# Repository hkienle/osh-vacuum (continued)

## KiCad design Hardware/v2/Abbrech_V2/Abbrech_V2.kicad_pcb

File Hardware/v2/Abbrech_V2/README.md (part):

# Abbrechplatine V2 – LED-Streifen und Taster

Stand 2026-11-11 (Rev B, Mouse Bites). Ein Nutzen 70 × 81,2 mm mit einem Satz Zubehör-Platinen. Die Teilplatinen und die
Taster sind nicht untereinander verdrahtet: jede/jeder hat eigene Netze, auch die beiden Taster der Doppeltaster-Platine.

| Reihe | Teilplatinen (je 15,3 mm breit) |
|---|---|
| 0 | LED A 56 mm: 10 × WS2812B-2020 (V6, C52917434) |
| 1 | LED B 56 mm: 5 × WS2812B-5050 (V6, C52917433), Raster 7,8 mm wie V1, Pads quer |
| 2 | Einzeltaster T1 (17,3 mm) · Doppeltaster T5/T6 (32,5 mm, zwei Stecker) |
| 3 | Einzeltaster T2 · T3 · T4 |

Ringsum 5 mm Rand mit drei Passermarken, zwischen den Platinen 2 mm Fräsnut, Stege 5 mm mit Mouse Bites.

## Entscheidungen (Thomas)
- 2026-11-10: Breite 15,3 mm wie V1; Taster mit Bohrung an einem Ende und Halbbohrung am anderen; Taster TS-1187A-C-A-B
  (Extended, 2,6 N statt 1,6 N beim Basic-Teil, Hub bei Taktschaltern immer ≈ 0,25 mm); Stecker nicht bestückt, JLC bestückt
  nur die Oberseite; Bestellung bei JLC.
- 2026-11-10: LEDs exakt mittig.
- 2026-11-11: 5050-Streifen mit 5 LEDs, Pads quer zum Streifen.
- 2026-11-11 (später): keine THT-Löcher; alle Schraublöcher nur als Halbbohrung an den Enden (LED und Taster);
  Taster auf der Doppeltaster-Platine weiter auseinander (wie zwei Einzeltaster am Stück).
- 2026-11-11 (später): Stege auch zwischen den Taster-Reihen; je Kante ein Steg am Einzeltaster, zwei am Doppeltaster;
  alle Taster um 90° gedreht (Pads längs).
- 2026-11-11 (später): LED-Streifen zusätzlich mit THT-PH, um 90° gedreht neben den LEDs (u 7 / 49); SMD-PH nach innen; Doppeltaster ebenfalls mit THT-PH.
- 2026-11-11 (später): Einzeltaster zusätzlich mit THT-PH (B2B-PH-K, stehend, bestückt, Unterseite, bündig mit
  der Kante) dort, wo vorher die Beschriftung stand; der SMD-PH bleibt als Footprint, DNP; alle Taster-Platinen gleich
  ausgerichtet. (Kurz danach geändert: alle Stecker der Unterseite DNP, auch die THT-PH, siehe unten.)
- 2026-11-12 (später): Doppeltaster-Platine 32,5 mm statt 36,67 mm lang, an beiden Enden je 2,08 mm kürzer; Taster,
  Stecker, Leiterbahnen und Stege bleiben exakt an ihrem Platz.
- 2026-11-12 (später): Stege 5 mm statt 3 mm breit (JLC verlangt mind. 5 mm), je Seite 6 statt 4 Mouse-Bite-Bohrungen;
  Lage der Stege unverändert.
- 2026-11-12: Doppeltaster näher zusammen: Tastermitten 15,00 mm (vorher 19,33 mm); Stege an der Steckerseite und
  Siebdruck unten (Figma, Beschriftung der Doppeltaster mitgerückt) angepasst.
- 2026-11-11 (Umbau Rev B): alle Ecken so groß wie sinnvoll gerundet; Platinen mit Mouse Bites verbinden (V1 brach viel zu
  schwer, V-Cut erlaubt keine runden Ecken); LED-Streifen genau 56 mm; SMD- und THT-Stecker getrennt (SMD unten unter den
  LEDs, THT neben dem Schraubloch zur Kante versetzt); Taster kürzer (Schraubenkopf Ø 6 mm); eine Reihe Einzeltaster und
  eine Doppeltaster-Platine mit zwei Steckern („zwei Einzeltaster am Stück“); ein Satz je Nutzen; 4 Einzeltaster; Taster
  untereinander nicht verdrahtet. Vorbild: Abbrechteil der V1 („so in der Art grob“).

## Umsetzung
- **Maße**: Breite 15,3 mm, LED-Streifen 56 mm (V1), Eckradius 5 mm. An jedem Ende mittig eine Halbbohrung Ø 3,0 mm.
  Einzeltaster 17,33 mm (drei Stück plus zwei Nuten = 56 mm), Eckradius 4,5 mm (sonst lägen die Haltelaschen des
  SMD-Steckers in der Ecke), Taster mittig mit Pads längs. Doppeltaster 32,5 mm lang (seit 2026-11-12; vorher 36,67 mm wie zwei Einzeltaster am Stück), mittig im alten Feld,
  Tastermitten 15,00 mm auseinander (je 8,75 mm vom Ende), GND-Fläche in der Mitte geteilt.
- **Schraubenkopf Ø 6 mm**: oben im Umkreis 3 mm um jede Halbbohrung keine Bauteile und keine Lötstellen.
- **Pinbelegung 1:1 wie Hauptplatine** (gerade PH-Kabel): LED 1 GND, 2 Daten, 3 5V (J60); Taster 1 Schalter, 2 GND
  (J50–J52). Beschriftung unten je Pin `G D +` bzw. `S G`, dazu `IN`/`OUT` oben und unten.
- **Taster T1–T6**: zusätzlich JST PH THT stehend (B2B-PH-K-S, C131337, nicht bestückt) auf der
  Unterseite, Gehäuse endet bündig mit der Kante (Lochreihe 2,85 mm von der Kante). Alle Taster-Platinen liegen gleich im
  Nutzen (Stecköffnung des SMD-PH oben).
- **LED-Streifen**: an beiden Enden zusätzlich JST PH THT stehend (B3B-PH-K-S, C131339, nicht bestückt, Unterseite), um 90°
  gedreht (Lochreihe quer bei u 7 / 49, neben den LEDs); die SMD-PH (DNP) sitzen weiter
  innen bei u 20 / 36.
- **Stecker**: je Anschluss ein JST PH SMD liegend (S3B/S2B-PH-SM4-TB, nicht bestückt) auf der Unterseite unter den LEDs
  bzw. unter dem Taster, Öffnung bündig zur Längskante (0,65 mm zurück). Keine THT-Löcher.
- **LED-Streifen**: LEDs mittig, Datenkette von IN (rechts) nach OUT (links), 100 nF je LED, 10 µF am Eingang,
  5V-Schiene oben 0,8 mm, Einspeisung von beiden Steckern, GND-Flächen oben und unten.
  5050: VDD/DO oben, GND/DI unten, Daten mit 45° durch die Lücken, 100 nF senkrecht in der Lücke auf der Eingangsseite
  jeder LED. 2020: 100 nF längs über der LED, Pad 1 genau über dem VDD-Pad. 10 µF senkrecht zwischen THT-Stecker (Ausgang)
  und der ersten LED, Pad 1 auf der Schiene (Thomas 2026-11-11: weg vom Rand, kompakter).
- **Nutzen**: Fräsnut 2 mm, Stege 5 mm (Footprint `Abbrech_V2:MouseBites_Steg5mm_Nut2mm`: je Seite 6 NPTH Ø 0,5 mm im
  Raster 0,8 mm, Mitte 0,25 mm in der Platine, so bricht der Steg an der Platinenkante). Stege nur an den Längskanten (die
  Stirnseiten haben Halbbohrungen). LED-Streifen: drei Stege je Längskante zwischen den Stecköffnungen. Taster: je Kante
  ein Steg mittig unter dem Taster (Doppeltaster zwei); an der Steckerseite sitzt er mittig vor dem Stecker zwischen den
  Haltelaschen – der Stecker ist unten, das Gegenstück wird unter der Platine eingeschoben, ein Steg-Rest stört nicht.
  Die Sperrfläche des SMD-PH ragt dabei über die Kante (Gehäuse endet 0,15 mm vor den Bohrungen); deshalb ist die
  DRC-Prüfung „NPTH in Sperrfläche“ auf „ignorieren“ gestellt. Innenecken der Stege R 0,5 mm.
- **Siebdruck der LEDs**: Umrisse aller LEDs auf F.Fab (die Abblock-Kondensatoren sitzen dicht daneben); deshalb ist die DRC-Prüfung „Footprint weicht von Bibliothek ab“ auf „ignorieren“ gestellt.
- **3D-Modelle** für WS2812B-2020, TS-1187A und die PH-SMD-Stecker aus der JLCEDA/EasyEDA Official Library
  (https://lceda.cn/, https://easyeda.com), KiCad 10 liefert sie nicht mit; Herkunft in `3d/QUELLE.md`. Renders in
  `Review/abbrech/`.

- **Siebdruck oben und unten aus Figma** (2026-11-11): Rahmen „Abbrechplatine oben – Siebdruck“ und „Abbrechplatine
  unten – Siebdruck (Ansicht von unten)“ auf der Seite „Platine“ (Figma-Datei der Hauptplatine). Render schwarz, 20 px/mm,
  deckt genau den Nutzen ab; Ebene „Siebdruck (weiß = Druck)“. Export als SVG ohne Render nach
  `tools/abbrech/assets/silk_oben.svg` / `silk_unten.svg`, `gen_pcb.py` setzt sie als Flächen (unten gespiegelt) und lässt
  die generierten Texte weg. Schrift Jost Black (Netto Pro ist über die Figma-Schnittstelle nicht ladbar; in Figma
  umstellbar, dann neu exportieren).
- **STEP-Modelle** der herausgebrochenen Teilplatinen (ohne DNP-Teile): `step/Abbrech_LED_2020.step`,
  `Abbrech_LED_5050.step`, `Abbrech_Taster_einzeln.step`, `Abbrech_Taster_doppelt.step`, erzeugt mit
  `tools/abbrech/export_step.py` (KiCad-Python, aus 05_Hardware).

## Erzeugen und Prüfen
Alles wird aus Skripten erzeugt (nicht in KiCad von Hand ändern, sonst überschreibt der nächste Lauf die Änderung):

```
zsh tools/abbrech/build.sh                                   # Schaltplan, Layout, Flächen füllen, ERC + DRC mit Schaltplan-Abgleich
zsh tools/abbrech/fertigung.sh Fertigung/Abbrech_aktuell     # JLC: Gerber-ZIP, BOM, CPL (zu jedem Commit neu)
```
(beides aus `05_Hardware`). Stand 2026-11-11: ERC 0, DRC 0, Abgleich 0.

## Bestellung bei JLC
- 2 Lagen, 1,6 mm, 1 oz, Farbe wie Hauptplatine; „Panel by Customer“ (Nutzen mit Fräsnuten und Mouse Bites, keine
  V-Cuts); Vias „Tented“.
- „Different Design“: 4 (LED 2020, LED 5050, Einzeltaster, Doppeltaster).
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
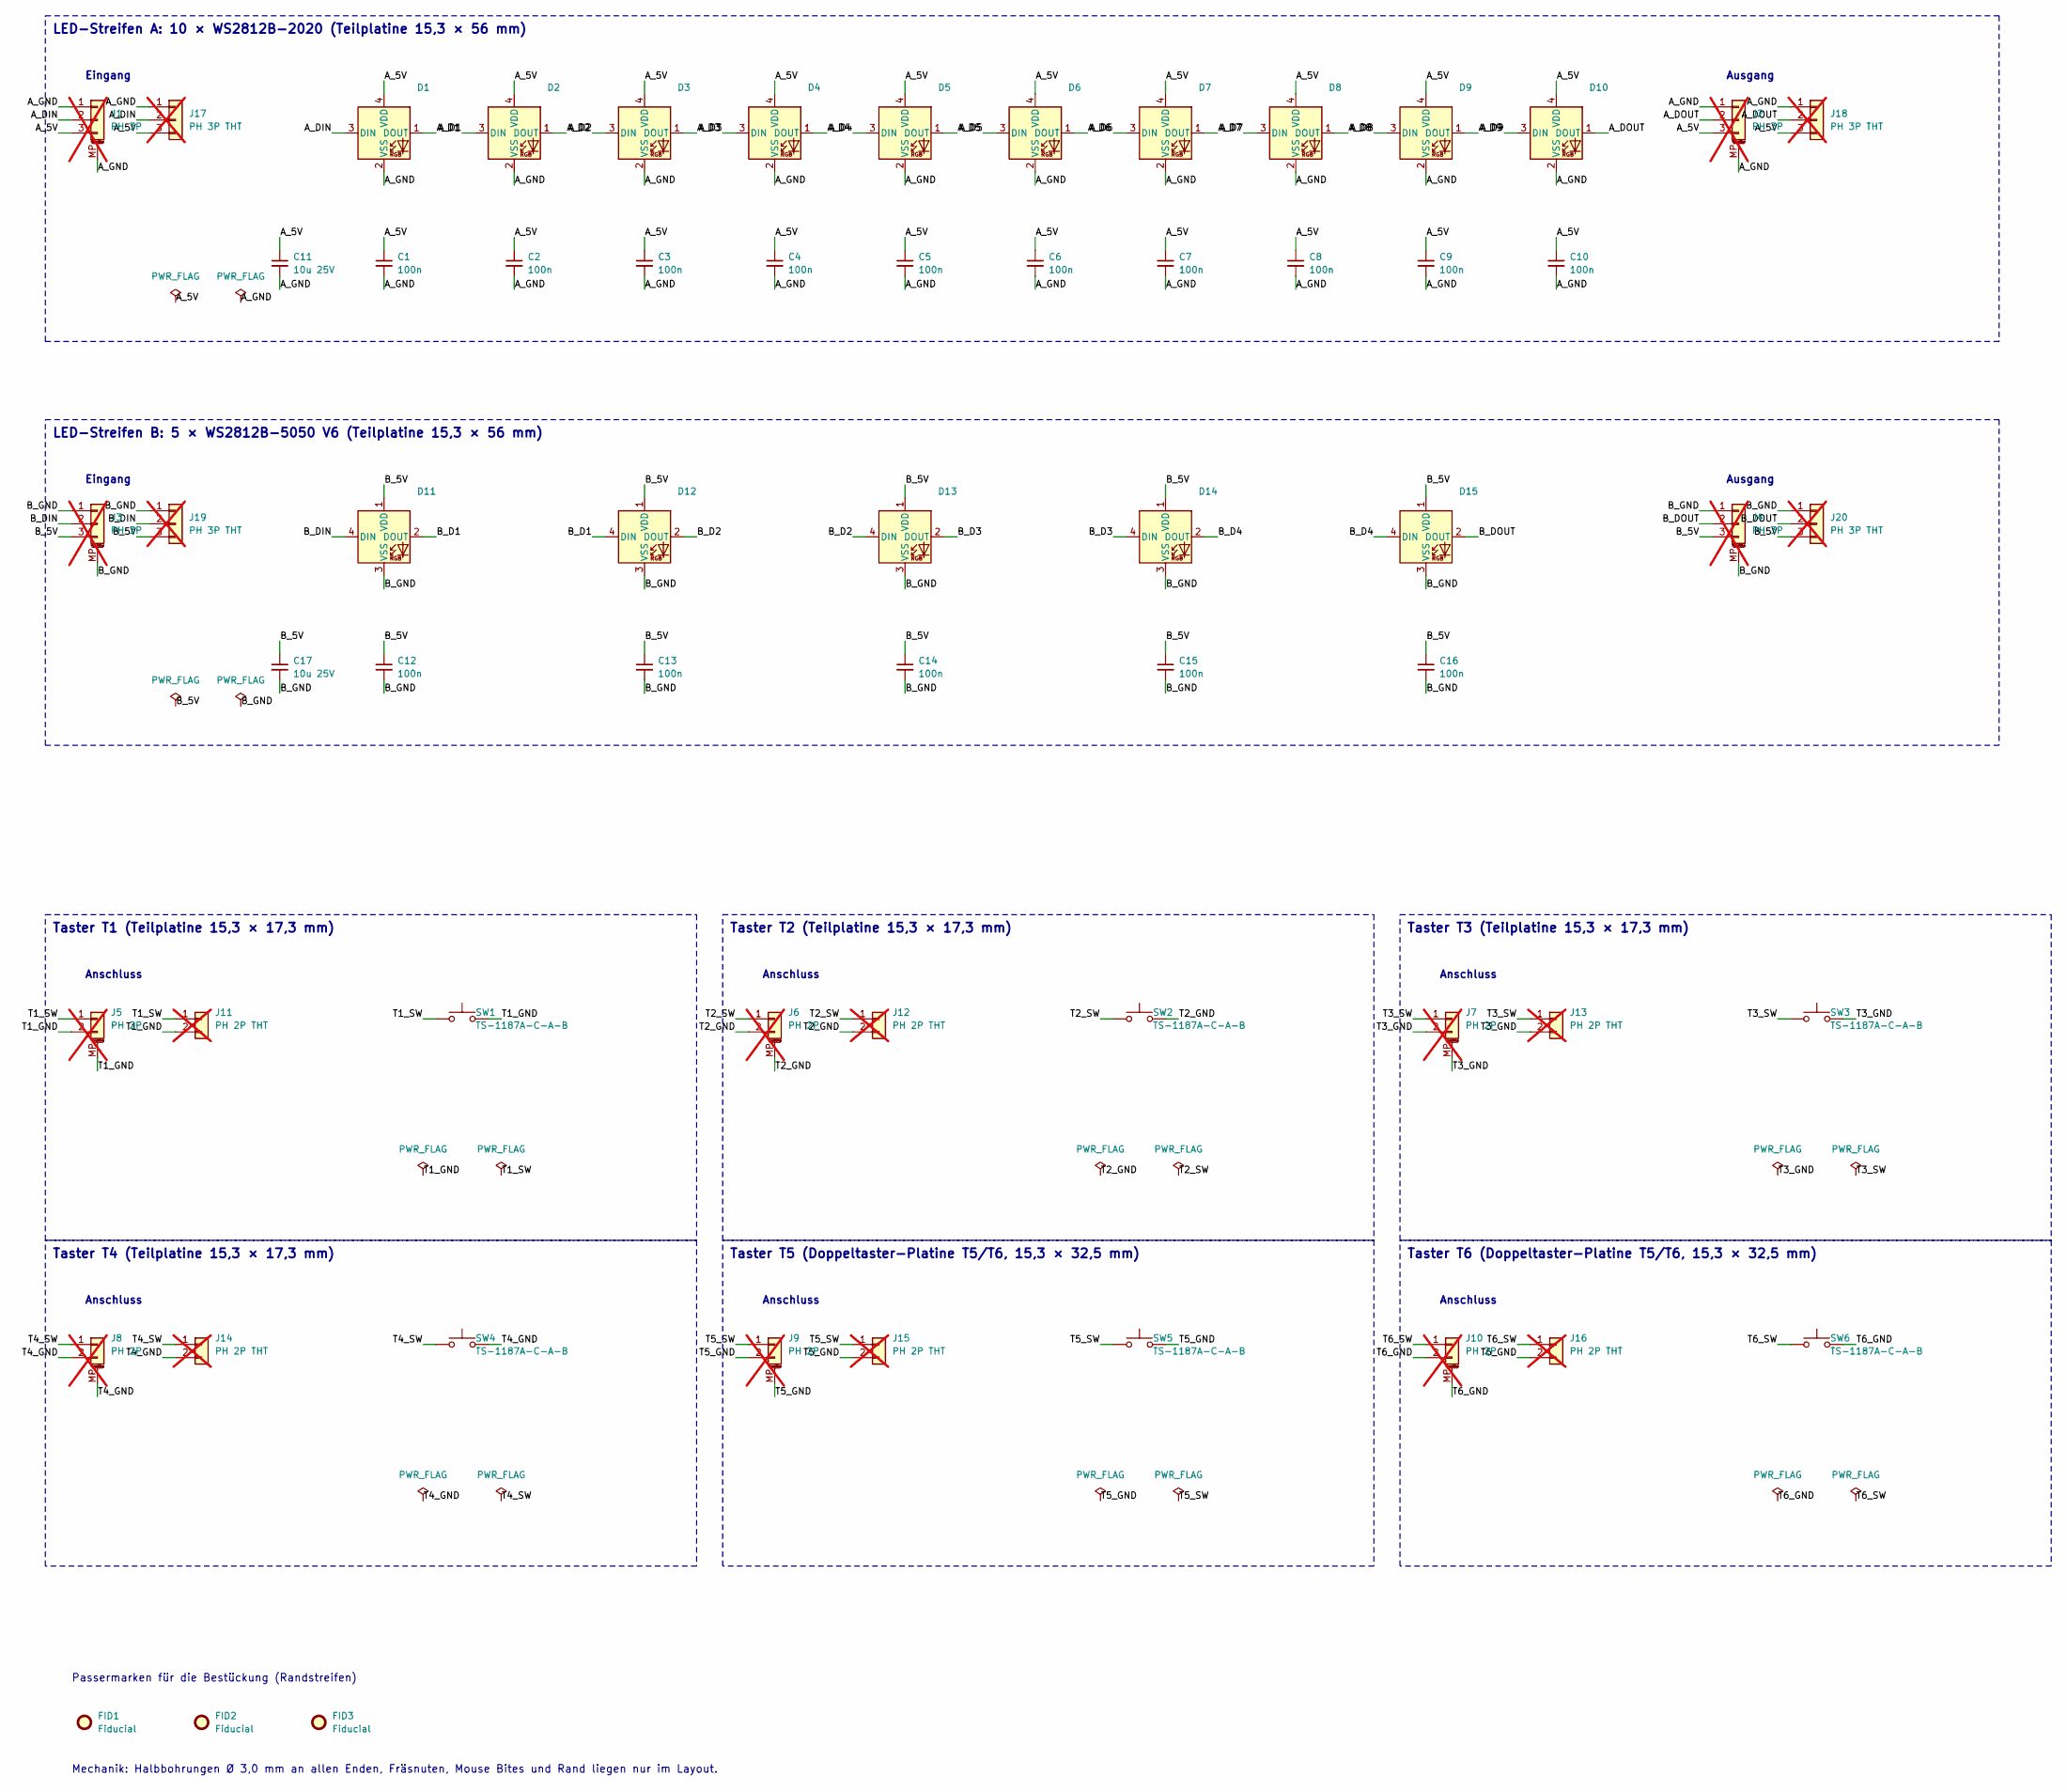
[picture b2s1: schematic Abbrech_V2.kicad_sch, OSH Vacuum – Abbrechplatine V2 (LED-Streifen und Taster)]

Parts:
C1, C2, C3, C4, C5, C6, C7, C8, C9, C10, C12, C13, C14, C15, C16: 100n; C_0402_1005Metric; MPN CL05B104KO5NNNC; LCSC C1525
C11, C17: 10u 25V; C_0603_1608Metric; MPN CL10A106MA8NRNC; LCSC C96446
D1, D2, D3, D4, D5, D6, D7, D8, D9, D10: WS2812B-2020; LED_WS2812B-2020_PLCC4_2.0x2.0mm; MPN WS2812B-2020-V6; LCSC C52917434
D11, D12, D13, D14, D15: WS2812B-5050; LED_WS2812B_PLCC4_5.0x5.0mm_P3.2mm; MPN WS2812B-V6; LCSC C52917433
FID1, FID2, FID3: Fiducial; Fiducial_1mm_Mask2mm
J1, J2, J3, J4: PH 3P; JST_PH_S3B-PH-SM4-TB_1x03-1MP_P2.00mm_Horizontal; MPN S3B-PH-SM4-TB(LF)(SN); LCSC C265101; not fitted
J5, J6, J7, J8, J9, J10: PH 2P; JST_PH_S2B-PH-SM4-TB_1x02-1MP_P2.00mm_Horizontal; MPN S2B-PH-SM4-TB(LF)(SN); LCSC C295747; not fitted
J11, J12, J13, J14, J15, J16: PH 2P THT; JST_PH_B2B-PH-K_1x02_P2.00mm_Vertical; MPN B2B-PH-K-S(LF)(SN); LCSC C131337; not fitted
J17, J18, J19, J20: PH 3P THT; JST_PH_B3B-PH-K_1x03_P2.00mm_Vertical; MPN B3B-PH-K-S(LF)(SN); LCSC C131339; not fitted
SW1, SW2, SW3, SW4, SW5, SW6: TS-1187A-C-A-B; SW_Push_1P1T_XKB_TS-1187A; MPN TS-1187A-C-A-B; LCSC C480267

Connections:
/A_5V: C1.1, C2.1, C3.1, C4.1, C5.1, C6.1, C7.1, C8.1, C9.1, C10.1, C11.1, D1.4 (VDD), D2.4 (VDD), D3.4 (VDD), D4.4 (VDD), D5.4 (VDD), D6.4 (VDD), D7.4 (VDD), D8.4 (VDD), D9.4 (VDD), D10.4 (VDD), J1.3, J2.3, J17.3, J18.3
/A_D1: D1.1 (DOUT), D2.3 (DIN)
/A_D2: D2.1 (DOUT), D3.3 (DIN)
/A_D3: D3.1 (DOUT), D4.3 (DIN)
/A_D4: D4.1 (DOUT), D5.3 (DIN)
/A_D5: D5.1 (DOUT), D6.3 (DIN)
/A_D6: D6.1 (DOUT), D7.3 (DIN)
/A_D7: D7.1 (DOUT), D8.3 (DIN)
/A_D8: D8.1 (DOUT), D9.3 (DIN)
/A_D9: D9.1 (DOUT), D10.3 (DIN)
/A_DIN: D1.3 (DIN), J1.2, J17.2
/A_DOUT: D10.1 (DOUT), J2.2, J18.2
/A_GND: C1.2, C2.2, C3.2, C4.2, C5.2, C6.2, C7.2, C8.2, C9.2, C10.2, C11.2, D1.2 (VSS), D2.2 (VSS), D3.2 (VSS), D4.2 (VSS), D5.2 (VSS), D6.2 (VSS), D7.2 (VSS), D8.2 (VSS), D9.2 (VSS), D10.2 (VSS), J1.1, J1.MP (MountPin), J2.1, J2.MP (MountPin), J17.1, J18.1
/B_5V: C12.1, C13.1, C14.1, C15.1, C16.1, C17.1, D11.1 (VDD), D12.1 (VDD), D13.1 (VDD), D14.1 (VDD), D15.1 (VDD), J3.3, J4.3, J19.3, J20.3
/B_D1: D11.2 (DOUT), D12.4 (DIN)
/B_D2: D12.2 (DOUT), D13.4 (DIN)
/B_D3: D13.2 (DOUT), D14.4 (DIN)
/B_D4: D14.2 (DOUT), D15.4 (DIN)
/B_DIN: D11.4 (DIN), J3.2, J19.2
/B_DOUT: D15.2 (DOUT), J4.2, J20.2
/B_GND: C12.2, C13.2, C14.2, C15.2, C16.2, C17.2, D11.3 (VSS), D12.3 (VSS), D13.3 (VSS), D14.3 (VSS), D15.3 (VSS), J3.1, J3.MP (MountPin), J4.1, J4.MP (MountPin), J19.1, J20.1
/T1_GND: J5.2, J5.MP (MountPin), J11.2, SW1.2
/T1_SW: J5.1, J11.1, SW1.1
/T2_GND: J6.2, J6.MP (MountPin), J12.2, SW2.2
/T2_SW: J6.1, J12.1, SW2.1
/T3_GND: J7.2, J7.MP (MountPin), J13.2, SW3.2
/T3_SW: J7.1, J13.1, SW3.1
/T4_GND: J8.2, J8.MP (MountPin), J14.2, SW4.2
/T4_SW: J8.1, J14.1, SW4.1
/T5_GND: J9.2, J9.MP (MountPin), J15.2, SW5.2
/T5_SW: J9.1, J15.1, SW5.1
/T6_GND: J10.2, J10.MP (MountPin), J16.2, SW6.2
/T6_SW: J10.1, J16.1, SW6.1

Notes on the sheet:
LED-Streifen A: 10 × WS2812B-2020 (Teilplatine 15,3 × 56 mm)
Eingang
Ausgang
LED-Streifen B: 5 × WS2812B-5050 V6 (Teilplatine 15,3 × 56 mm)
Taster T1 (Teilplatine 15,3 × 17,3 mm)
Anschluss
Taster T2 (Teilplatine 15,3 × 17,3 mm)
Taster T3 (Teilplatine 15,3 × 17,3 mm)
Taster T4 (Teilplatine 15,3 × 17,3 mm)
Taster T5 (Doppeltaster-Platine T5/T6, 15,3 × 32,5 mm)
Taster T6 (Doppeltaster-Platine T5/T6, 15,3 × 32,5 mm)
Passermarken für die Bestückung (Randstreifen)
Mechanik: Halbbohrungen Ø 3,0 mm an allen Enden, Fräsnuten, Mouse Bites und Rand liegen nur im Layout.

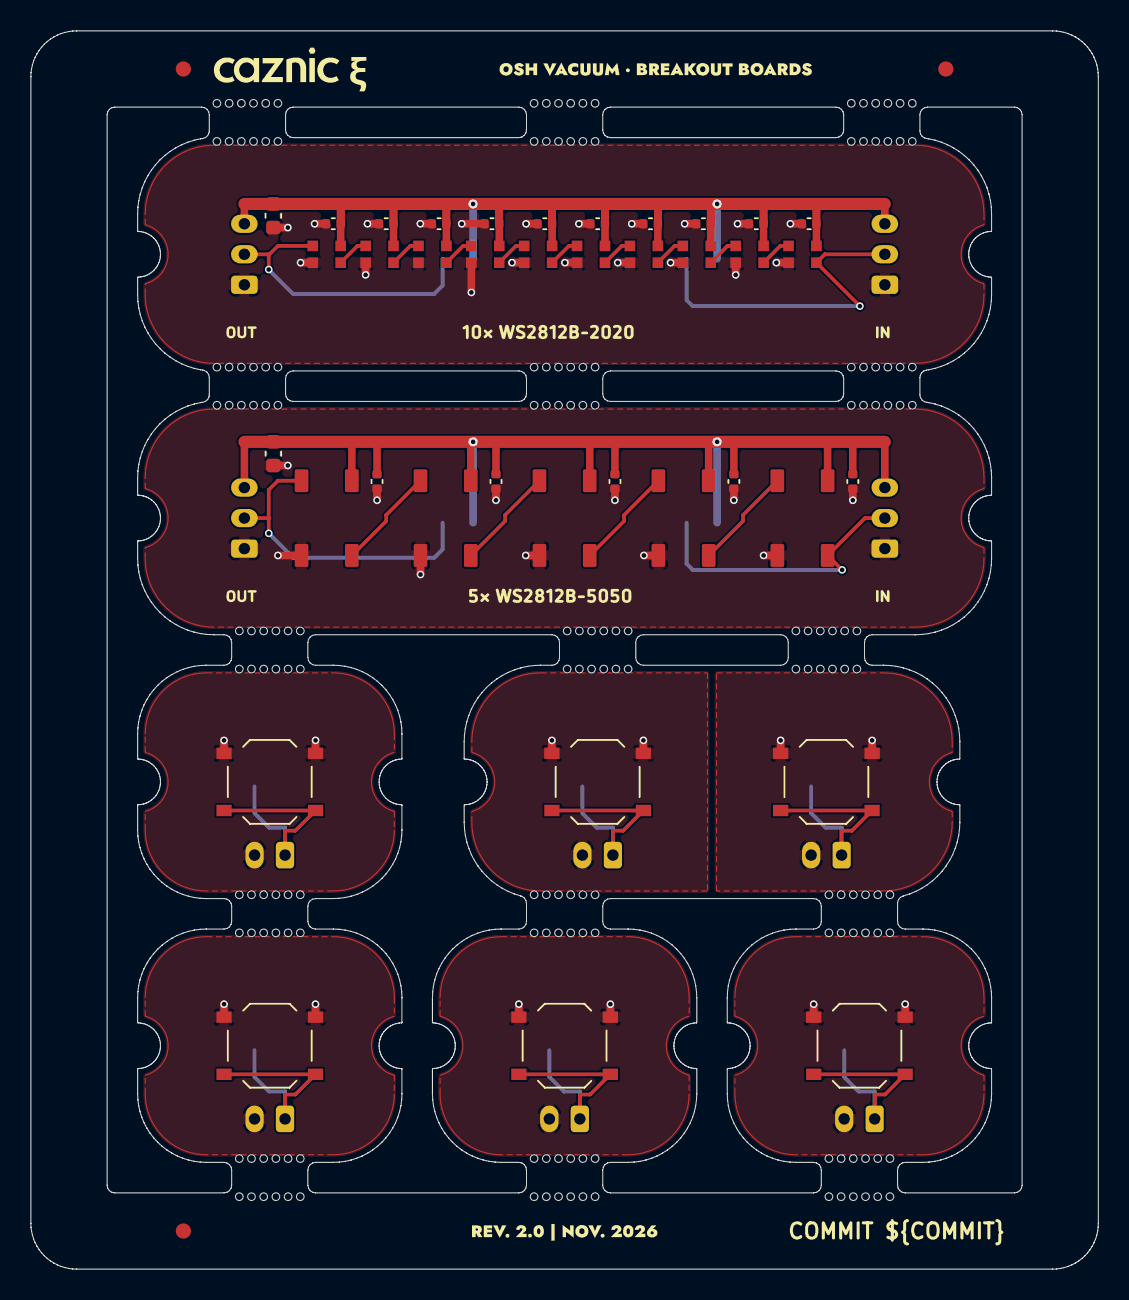
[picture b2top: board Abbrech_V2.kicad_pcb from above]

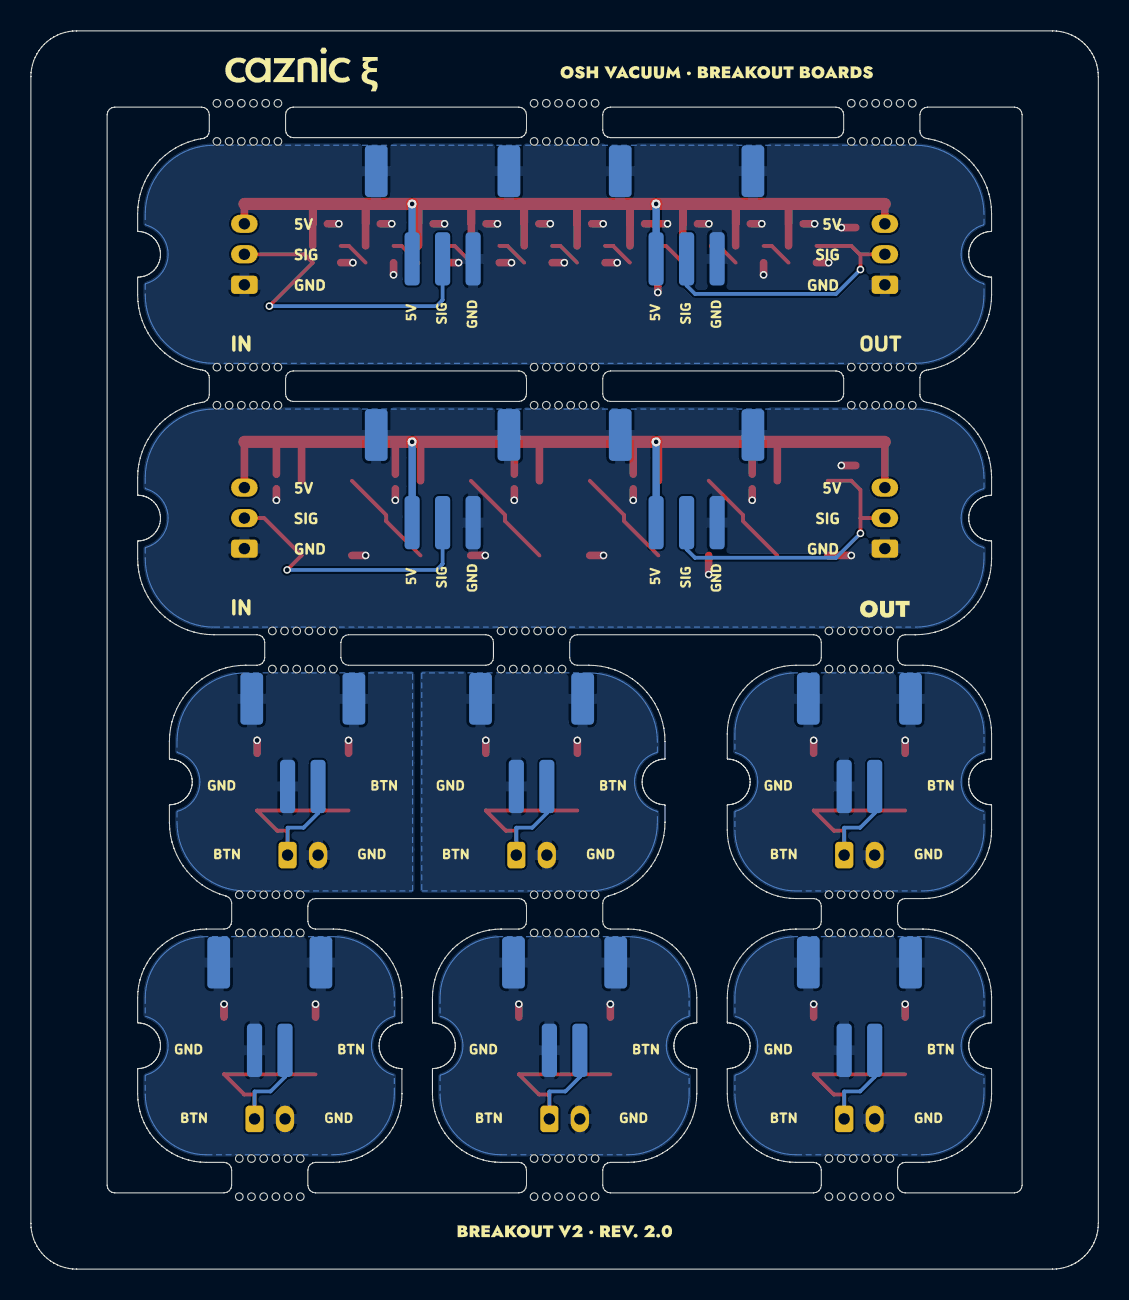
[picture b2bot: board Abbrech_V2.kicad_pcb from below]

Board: 2 copper layers, 70.0 x 81.2 mm, 76 parts (20 on the bottom side), 33 nets.

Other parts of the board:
MB1, MB2, MB3, MB4, MB5, MB6, MB7, MB8, MB9, MB10, MB11, MB12, MB13, MB14, MB15: MouseBites_Steg5mm_Nut2mm

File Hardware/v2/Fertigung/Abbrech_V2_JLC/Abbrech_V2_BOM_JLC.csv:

Comment,Designator,Footprint,LCSC Part #
100n,"C1,C10,C12,C13,C14,C15,C16,C2,C3,C4,C5,C6,C7,C8,C9",C_0402_1005Metric,C1525
TS-1187A-C-A-B,"SW1,SW2,SW3,SW4,SW5,SW6",SW_Push_1P1T_XKB_TS-1187A,C480267
WS2812B-5050,"D11,D12,D13,D14,D15",LED_WS2812B_PLCC4_5.0x5.0mm_P3.2mm,C52917433
WS2812B-2020,"D1,D10,D2,D3,D4,D5,D6,D7,D8,D9",LED_WS2812B-2020_PLCC4_2.0x2.0mm,C52917434
10u 25V,"C11,C17",C_0603_1608Metric,C96446

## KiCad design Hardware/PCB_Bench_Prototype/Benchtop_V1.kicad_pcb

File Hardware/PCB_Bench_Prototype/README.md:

# PCB Bench Prototype

**Status: Untested** - This board is currently in the benchtop prototype phase of the Open Source Vacuum Cleaner project and has not yet been tested.

## Overview

This PCB is designed to control a high RPM impeller for vacuum machines. It provides comprehensive control and monitoring capabilities with modern connectivity options.

The design features break-off sections that allow users to build their own vacuum cleaner in whichever shape they like. These break-off sections enable flexible placement of LEDs and buttons to suit various form factors and user preferences.

## Features

- **Connectivity**
  - BLE (Bluetooth Low Energy)
  - WiFi connectivity
  
- **Power Management**
  - USB-C connector for programming
  - Voltage regulation from 15-32V down to 5V and 3.3V
  - Battery voltage monitoring (reads voltage of connected battery)
  
- **User Interface**
  - 5 RGB LEDs (WS2812B)
  - 3 customizable buttons
  
- **Motor Control & Monitoring**
  - Automotive ProFet by Infineon for high-side switching (required for ESC control, replacing classic MOSFETs)
  - Level-shifted 3.3V and 5V PWM output
  - Voltage-divided input for 5V tachometer signal
  - 10kΩ thermistor reading capability
  
- **Expansion**
  - All unused and safe GPIOs are broken out
  - I2C, SPI, and UART interfaces available

## Bill of Materials (BOM)

| Designator | Footprint | Quantity | Value | LCSC Part # |
|------------|-----------|----------|-------|-------------|
| C1, C7, C8, C9 | 0805 | 4 | 22µF | - |
| C10, C11, C12, C13, C14, C2, C5 | 0805 | 7 | 0.1µF | - |
| C3 | 0805 | 1 | 1µF | - |
| C4 | 0805 | 1 | 10nF | - |
| C6 | 0805 | 1 | 10µF | - |
| LED1, LED2, LED3, LED4, LED5 | LED-SMD_4P-L5.0-W5.0-TL-1 | 5 | WS2812B-V5/W | C2874885 |
| R10 | 0805 | 1 | 330kΩ | - |
| R11 | 0805 | 1 | 33kΩ | - |
| R12 | 0805 | 1 | 56kΩ | - |
| R13 | 0805 | 1 | 4.7kΩ | - |
| R14, R16 | 0805 | 2 | 5.1kΩ | - |
| R15, R17, R18, R3, R5, R6, R7, R8 | 0805 | 8 | 10kΩ | - |
| R4 | 0805 | 1 | 220Ω | - |
| R9 | 0805 | 1 | 22kΩ | - |
| SW1, SW2 | SW-SMD_4P-L4.2-W3.2-P2.15-LS4.6 | 2 | RKB2SJK250SMTRLFS | C2927789 |
| SW6, SW7, SW8 | KEY-SMD_4P-L5.2-W5.2-P3.7-LS6.4-TL | 3 | TS-1076S-A7B3 | C492950 |
| U1 | WIRELM-SMD_ESP32-S3-WROOM-1 | 1 | ESP32-S3-WROOM-1(N16R2) | C2913205 |
| U2 | PG-HSOF-8_L10.4-W9.8-BTH500151LUAAUMA1 | 1 | BTH500151LUAAUMA1 | C36571656 |
| U3 | SOT-223-4_L6.5-W3.5-P2.30-LS7.0-BR | 1 | LD1117S33CTR | C35879 |
| U4, U5 | SC-70-5_L2.0-W1.3-P0.65-LS2.1-BL | 2 | SN74AHCT1G125DCKR | C350557 |
| U8 | PWRM-TH_L11.7-W7.5_TSR1-2450 | 1 | TSR 1-2450_C6886877 | C6886877 |
| U9 | USB-SMD_TYPE-C16PIN-1 | 1 | 12402012E212A | C5150972 |

## Images

### Front View

### Back View

### PCB Layout

## License

This hardware design is licensed under the **CERN Open Hardware Licence - Strongly Reciprocal (CERN OHL-S v2)**.

The full license text is available at: [cern_ohl_s_v2.txt](https://gitlab.com/ohwr/project/cernohl/-/wikis/uploads/819d71bea3458f71fba6cf4fb0f2de6b/cern_ohl_s_v2.txt)

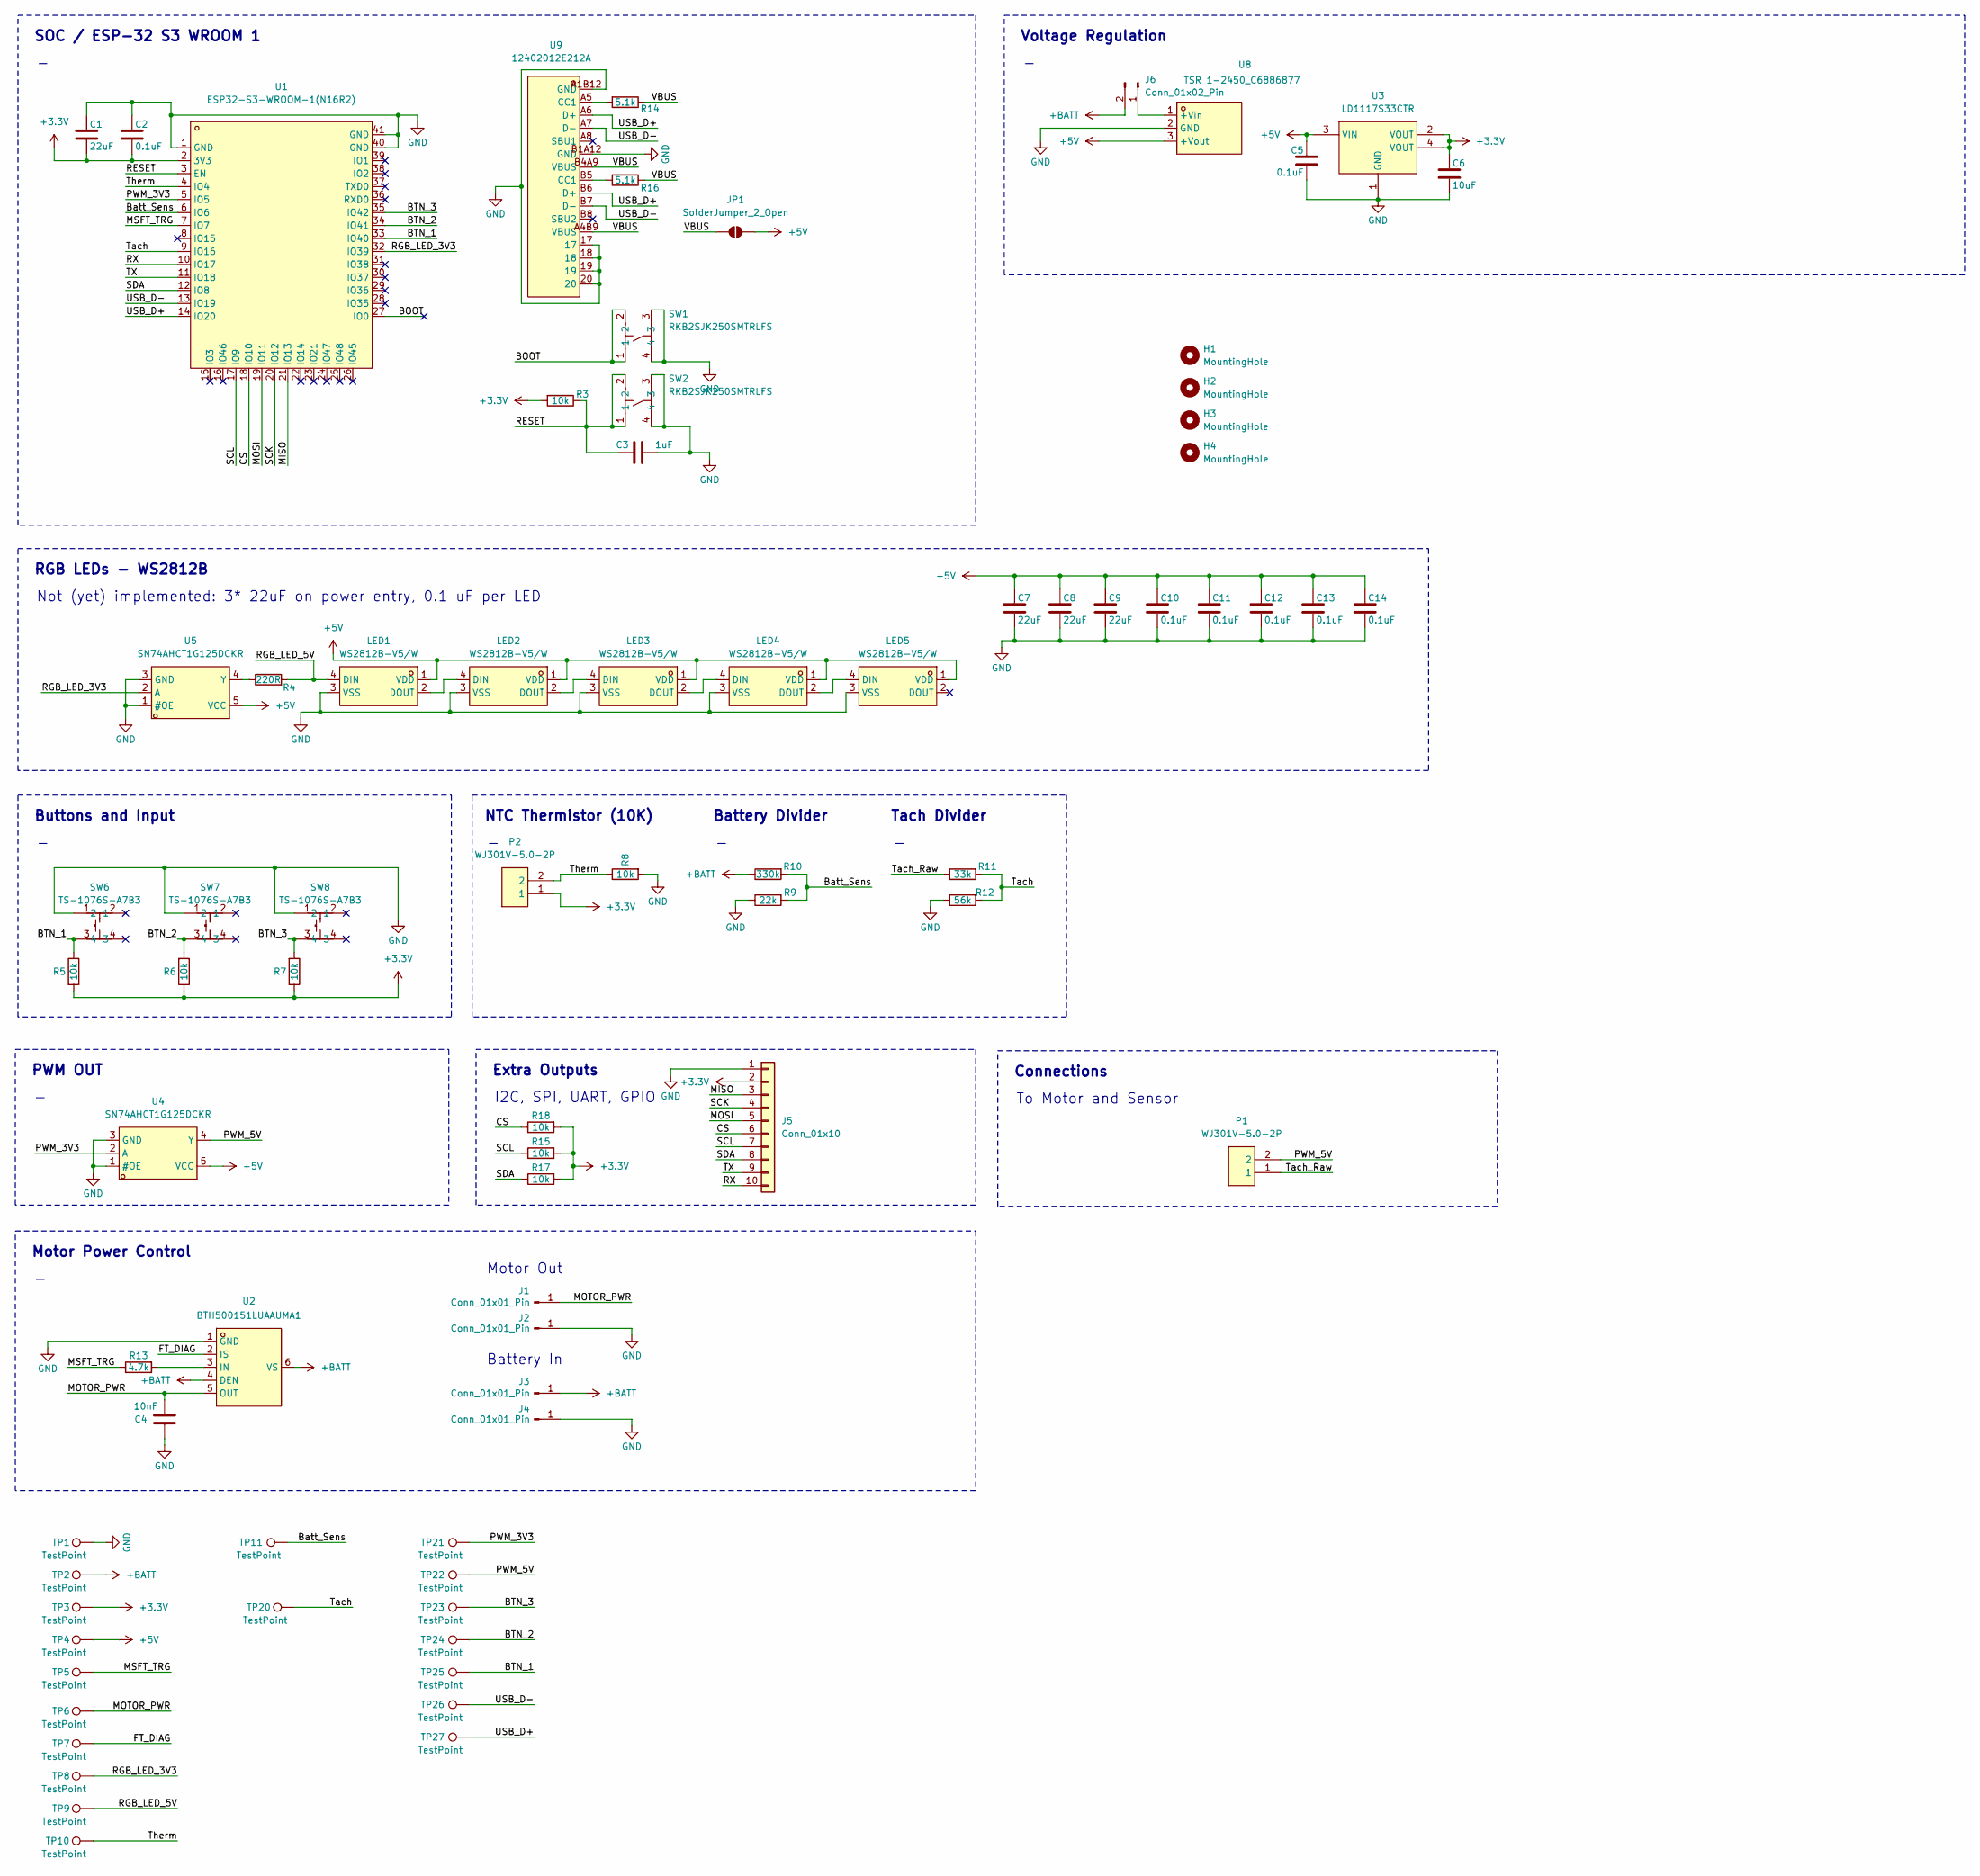
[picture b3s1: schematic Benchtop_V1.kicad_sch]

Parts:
C1, C7, C8, C9: 22uF; R_0805_2012Metric_Pad1.20x1.40mm_HandSolder
C2, C5, C10, C11, C12, C13, C14: 0.1uF; R_0805_2012Metric_Pad1.20x1.40mm_HandSolder
C3: 1uF; R_0805_2012Metric_Pad1.20x1.40mm_HandSolder
C4: 10nF; R_0805_2012Metric_Pad1.20x1.40mm_HandSolder
C6: 10uF; R_0805_2012Metric_Pad1.20x1.40mm_HandSolder
H1, H2, H3, H4: MountingHole; MountingHole_3.2mm_M3_Pad_Via
J1, J2, J3, J4: Conn_01x01_Pin; SolderWirePad_1x01_SMD_5x10mm
J5: Conn_01x10; PinHeader_2x05_P2.54mm_Vertical
J6: Conn_01x02_Pin; PinHeader_1x02_P2.54mm_Vertical
JP1: SolderJumper_2_Open; SolderJumper-2_P1.3mm_Open_Pad1.0x1.5mm
LED1, LED2, LED3, LED4, LED5: WS2812B-V5/W; LED-SMD_4P-L5.0-W5.0-TL-1; LCSC Part C2874885
P1, P2: WJ301V-5.0-2P; CONN-TH_2P-P5.00_WJ301V-5.00-2P; LCSC Part C8475
R3, R5, R6, R7, R8, R15, R17, R18: 10k; R_0805_2012Metric_Pad1.20x1.40mm_HandSolder
R4: 220R; R_0805_2012Metric_Pad1.20x1.40mm_HandSolder
R9: 22k; R_0805_2012Metric_Pad1.20x1.40mm_HandSolder
R10: 330k; R_0805_2012Metric_Pad1.20x1.40mm_HandSolder
R11: 33k; R_0805_2012Metric_Pad1.20x1.40mm_HandSolder
R12: 56k; R_0805_2012Metric_Pad1.20x1.40mm_HandSolder
R13: 4.7k; R_0805_2012Metric_Pad1.20x1.40mm_HandSolder
R14, R16: 5.1k; R_0805_2012Metric_Pad1.20x1.40mm_HandSolder
SW1, SW2: RKB2SJK250SMTRLFS; SW-SMD_4P-L4.2-W3.2-P2.15-LS4.6; LCSC Part C2927789
SW6, SW7, SW8: TS-1076S-A7B3; KEY-SMD_4P-L5.2-W5.2-P3.7-LS6.4-TL; LCSC Part C492950
TP1, TP2, TP3, TP4, TP5, TP6, TP7, TP8, TP9, TP10, TP11, TP20, TP21, TP22, TP23, TP24, TP25, TP26, TP27: TestPoint; TestPoint_Pad_D1.0mm
U1: ESP32-S3-WROOM-1(N16R2); WIRELM-SMD_ESP32-S3-WROOM-1; LCSC Part C2913205
U2: BTH500151LUAAUMA1; PG-HSOF-8_L10.4-W9.8-BTH500151LUAAUMA1; LCSC Part C36571656
U3: LD1117S33CTR; SOT-223-4_L6.5-W3.5-P2.30-LS7.0-BR; LCSC Part C35879
U4, U5: SN74AHCT1G125DCKR; SC-70-5_L2.0-W1.3-P0.65-LS2.1-BL; LCSC Part C350557
U8: TSR 1-2450_C6886877; PWRM-TH_L11.7-W7.5_TSR1-2450; LCSC Part C6886877
U9: 12402012E212A; USB-SMD_TYPE-C16PIN-1; LCSC Part C5150972

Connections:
+3.3V: C1.2, C2.2, C6.1, J5.2, P2.1, R3.2, R5.2, R6.1, R7.1, R15.2, R17.2, R18.2, TP3.1, U1.2 (3V3), U3.2 (VOUT), U3.4 (VOUT)
+5V: C5.1, C7.1, C8.1, C9.1, C10.1, C11.1, C12.1, C13.1, C14.1, JP1.2 (B), LED1.1 (VDD), LED2.1 (VDD), LED3.1 (VDD), LED4.1 (VDD), LED5.1 (VDD), TP4.1, U3.3 (VIN), U4.5 (VCC), U5.5 (VCC), U8.3 (+Vout)
+BATT: J3.1, J6.2, R10.1, TP2.1, U2.4 (DEN), U2.6 (VS)
/BOOT: SW1.1, SW1.2, U1.27 (IO0)
/BTN_1: R5.1, SW6.3, TP25.1, U1.33 (IO40)
/BTN_2: R6.2, SW7.3, TP24.1, U1.34 (IO41)
/BTN_3: R7.2, SW8.3, TP23.1, U1.35 (IO42)
/Batt_Sens: R9.2, R10.2, TP11.1, U1.6 (IO6)
/CS: J5.6, R18.1, U1.18 (IO10)
/FT_DIAG: TP7.1, U2.2 (IS)
/MISO: J5.3, U1.21 (IO13)
/MOSI: J5.5, U1.19 (IO11)
/MOTOR_PWR: C4.2, J1.1, TP6.1, U2.5 (OUT)
/MSFT_TRG: R13.1, TP5.1, U1.7 (IO7)
/PWM_3V3: TP21.1, U1.5 (IO5), U4.2 (A)
/PWM_5V: P1.2, TP22.1, U4.4 (Y)
/RESET: C3.1, R3.1, SW2.1, SW2.2, U1.3 (EN)
/RGB_LED_3V3: TP8.1, U1.32 (IO39), U5.2 (A)
/RGB_LED_5V: LED1.4 (DIN), R4.2, TP9.1
/RX: J5.10, U1.10 (IO17)
/SCK: J5.4, U1.20 (IO12)
/SCL: J5.7, R15.1, U1.17 (IO9)
/SDA: J5.8, R17.1, U1.12 (IO8)
/TX: J5.9, U1.11 (IO18)
/Tach: R11.2, R12.2, TP20.1, U1.9 (IO16)
/Tach_Raw: P1.1, R11.1
/Therm: P2.2, R8.1, TP10.1, U1.4 (IO4)
/USB_D+: TP27.1, U1.14 (IO20), U9.A6 (D+), U9.B6 (D+)
/USB_D-: TP26.1, U1.13 (IO19), U9.A7 (D-), U9.B7 (D-)
/VBUS: JP1.1 (A), R14.1, R16.1, U9.A4B9 (VBUS), U9.B4A9 (VBUS)
GND: C1.1, C2.1, C3.2, C4.1, C5.2, C6.2, C7.2, C8.2, C9.2, C10.2, C11.2, C12.2, C13.2, C14.2, J2.1, J4.1, J5.1, LED1.3 (VSS), LED2.3 (VSS), LED3.3 (VSS), LED4.3 (VSS), LED5.3 (VSS), R8.2, R9.1, R12.1, SW1.3, SW1.4, SW2.3, SW2.4, SW6.1, SW7.1, SW8.1, TP1.1, U1.1 (GND), U1.40 (GND), U1.41 (GND), U2.1 (GND), U3.1 (GND), U4.1 (#OE), U4.3 (GND), U5.1 (#OE), U5.3 (GND), U8.2 (GND), U9.17, U9.18, U9.19, U9.20, U9.A1B12 (GND), U9.B1A12 (GND)
unnamed: J6.1, U8.1 (+Vin)
unnamed: LED1.2 (DOUT), LED2.4 (DIN)
unnamed: LED2.2 (DOUT), LED3.4 (DIN)
unnamed: LED3.2 (DOUT), LED4.4 (DIN)
unnamed: LED4.2 (DOUT), LED5.4 (DIN)
unnamed: R14.2, U9.A5 (CC1)
unnamed: R16.2, U9.B5 (CC1)
unnamed: R13.2, U2.3 (IN)
unnamed: R4.1, U5.4 (Y)

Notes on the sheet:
PWM OUT
NTC Thermistor (10K)
Buttons and Input
Extra Outputs
Voltage Regulation
Motor Out
RGB LEDs - WS2812B
To Motor and Sensor
SOC / ESP-32 S3 WROOM 1
Motor Power Control
Not (yet) implemented: 3* 22uF on power entry, 0.1 uF per LED
Battery Divider
Battery In
I2C, SPI, UART, GPIO
Connections
Tach Divider

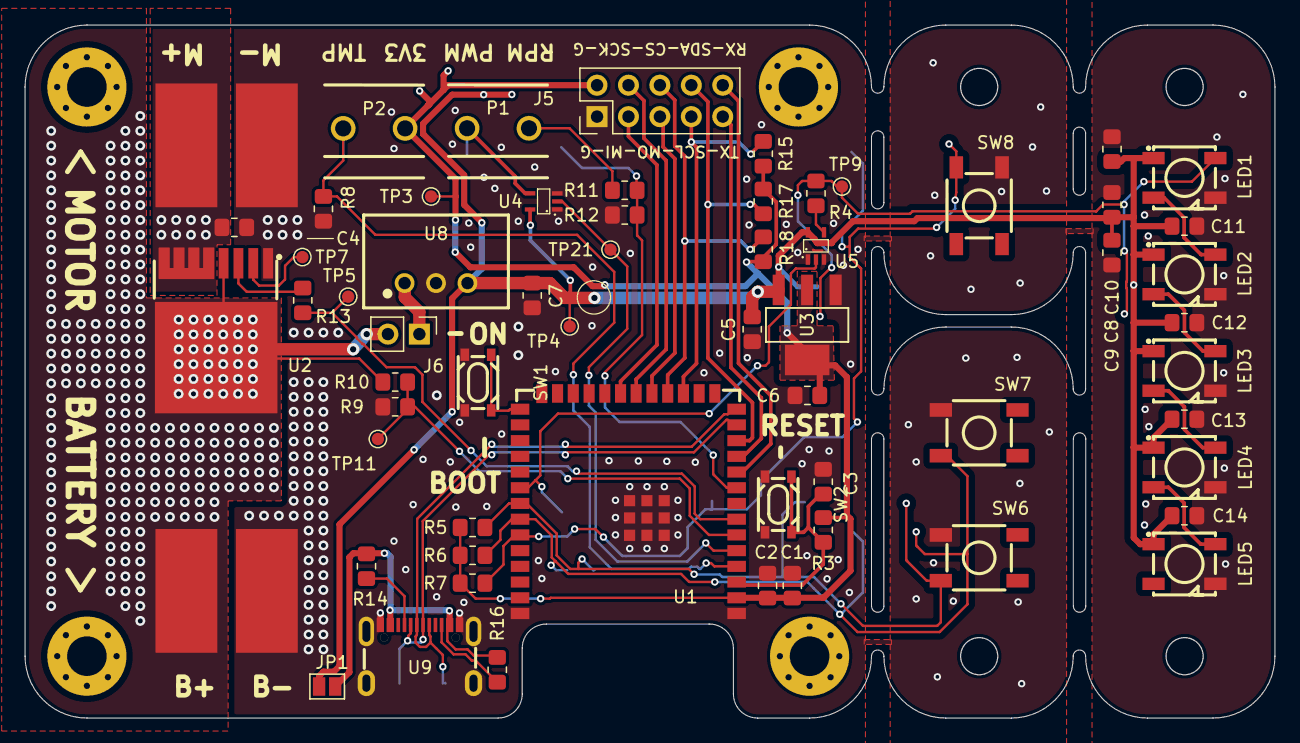
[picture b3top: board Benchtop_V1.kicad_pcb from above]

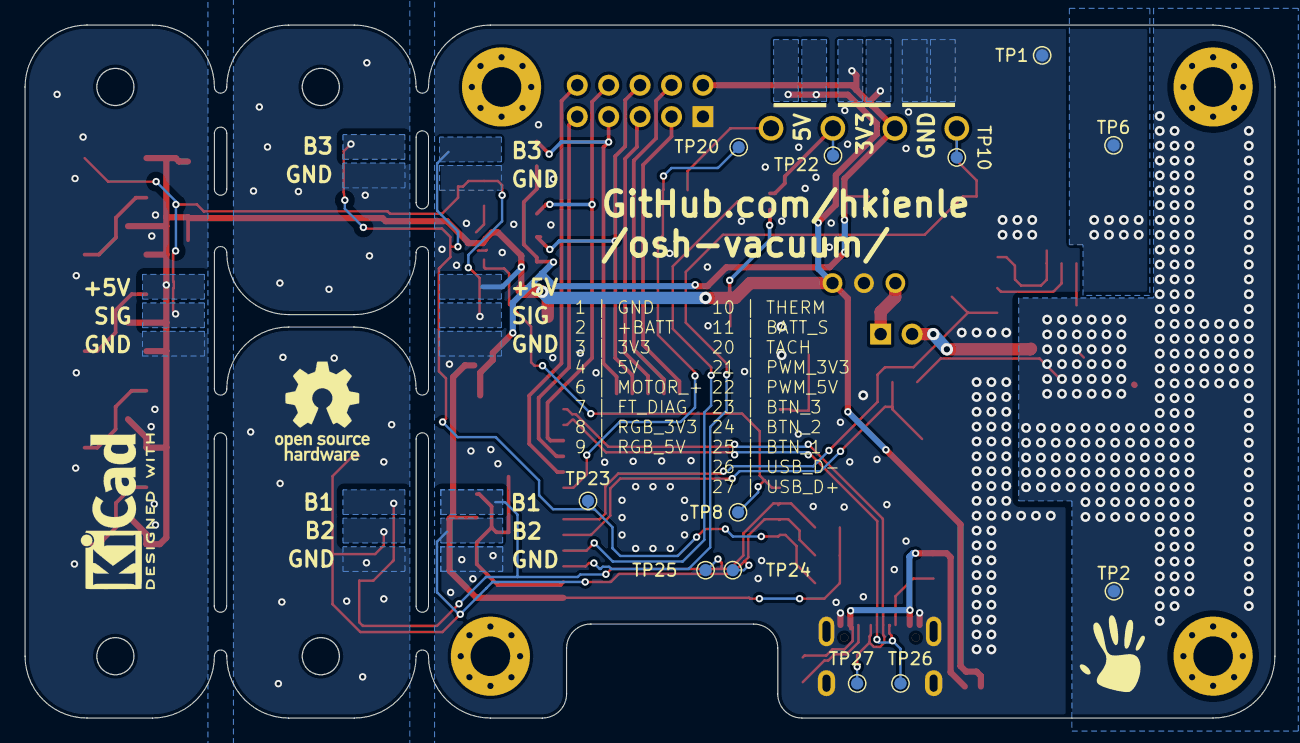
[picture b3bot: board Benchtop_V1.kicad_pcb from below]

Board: 2 copper layers, 101.0 x 56.0 mm, 79 parts (12 on the bottom side), 40 nets.

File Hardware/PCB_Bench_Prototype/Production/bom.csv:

Designator,Footprint,Quantity,Value,LCSC Part #
"C1, C7, C8, C9",0805,4,22uF,
"C10, C11, C12, C13, C14, C2, C5",0805,7,0.1uF,
C3,0805,1,1uF,
C4,0805,1,10nF,
C6,0805,1,10uF,
"J1, J2, J3, J4",SolderWirePad_1x01_SMD_5x10mm,4,Conn_01x01_Pin,
J5,PinHeader_2x05_P2.54mm_Vertical,1,Conn_01x10,
J6,PinHeader_1x02_P2.54mm_Vertical,1,Conn_01x02_Pin,
"LED1, LED2, LED3, LED4, LED5",LED-SMD_4P-L5.0-W5.0-TL-1,5,WS2812B-V5/W,C2874885
"P1, P2",CONN-TH_2P-P5.00_WJ301V-5.00-2P,2,WJ301V-5.0-2P,C8475
R10,0805,1,330k,
R11,0805,1,33k,
R12,0805,1,56k,
R13,0805,1,4.7k,
"R14, R16",0805,2,5.1k,
"R15, R17, R18, R3, R5, R6, R7, R8",0805,8,10k,
R4,0805,1,220R,
R9,0805,1,22k,
"SW1, SW2",SW-SMD_4P-L4.2-W3.2-P2.15-LS4.6,2,RKB2SJK250SMTRLFS,C2927789
"SW6, SW7, SW8",KEY-SMD_4P-L5.2-W5.2-P3.7-LS6.4-TL,3,TS-1076S-A7B3,C492950
"TP1, TP10, TP11, TP2, TP20, TP21, TP22, TP23, TP24, TP25, TP26, TP27, TP3, TP4, TP5, TP6, TP7, TP8, TP9",TestPoint_Pad_D1.0mm,19,TestPoint,
U1,WIRELM-SMD_ESP32-S3-WROOM-1,1,ESP32-S3-WROOM-1(N16R2),C2913205
U2,PG-HSOF-8_L10.4-W9.8-BTH500151LUAAUMA1,1,BTH500151LUAAUMA1,C36571656
U3,SOT-223-4_L6.5-W3.5-P2.30-LS7.0-BR,1,LD1117S33CTR,C35879
"U4, U5",SC-70-5_L2.0-W1.3-P0.65-LS2.1-BL,2,SN74AHCT1G125DCKR,C350557
U8,PWRM-TH_L11.7-W7.5_TSR1-2450,1,TSR 1-2450_C6886877,C6886877
U9,USB-SMD_TYPE-C16PIN-1,1,12402012E212A,C5150972
